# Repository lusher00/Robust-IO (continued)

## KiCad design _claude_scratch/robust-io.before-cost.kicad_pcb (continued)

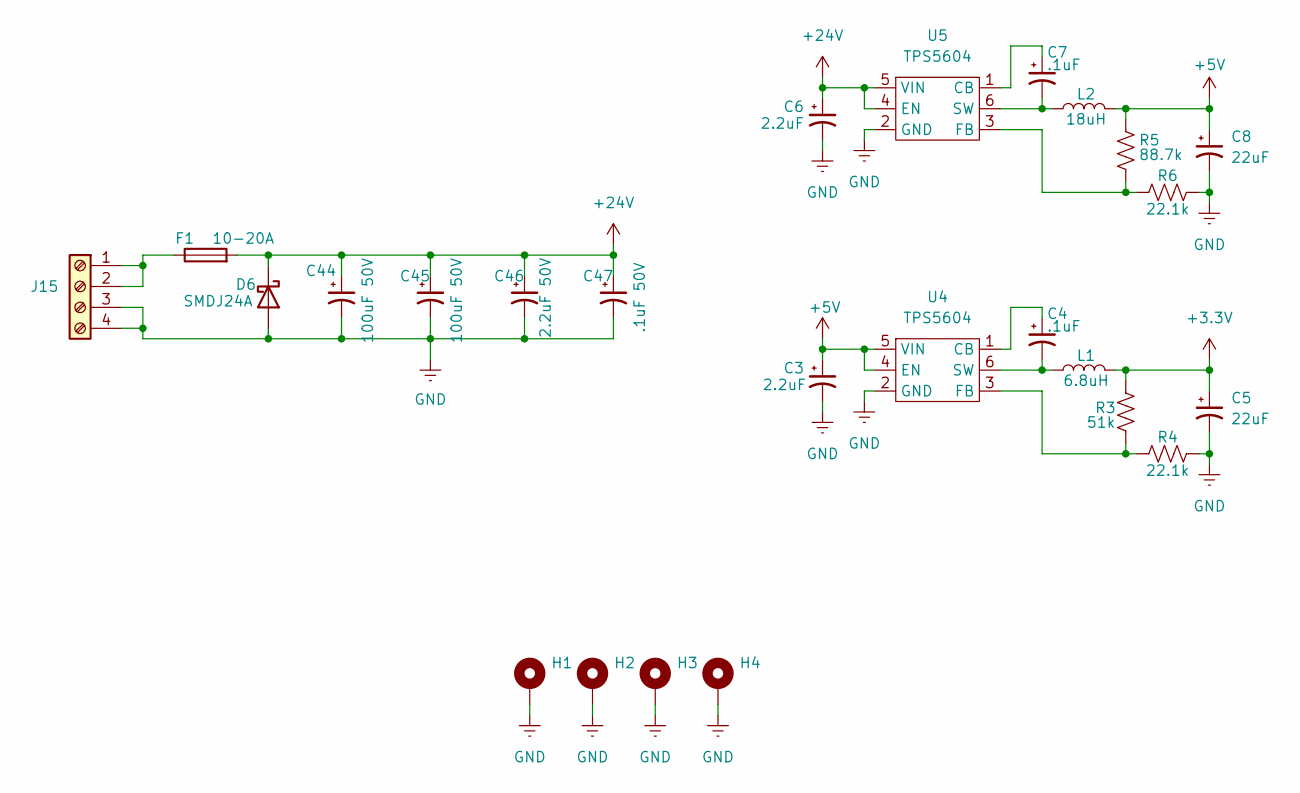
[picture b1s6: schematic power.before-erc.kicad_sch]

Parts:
C3, C6: 2.2uF; C_0805_2012Metric_Pad1.18x1.45mm_HandSolder
C4, C7: .1uF; C_0603_1608Metric_Pad1.08x0.95mm_HandSolder
C5, C8: 22uF; C_0603_1608Metric_Pad1.08x0.95mm_HandSolder
C44, C45: 100uF 50V; CP_Elec_8x10
C46: 2.2uF 50V; C_0805_2012Metric_Pad1.18x1.45mm_HandSolder
C47: .1uF 50V; C_0805_2012Metric_Pad1.18x1.45mm_HandSolder
D6: SMDJ24A; D_SMC
F1: 10-20A; Fuseholder_Blade_Mini_Keystone_3568
H1, H2, H3, H4: MountingHole_Pad; MountingHole_3.2mm_M3_DIN965_Pad_TopBottom
J15: Screw_Terminal_01x04; PhoenixContact_MSTBA_2,5_4-G-5,08_1x04_P5.08mm_Horizontal
L1: 6.8uH; L_0805_2012Metric_Pad1.05x1.20mm_HandSolder; Part Number CB2016T6R8M
L2: 18uH; L_0805_2012Metric
R3: 51k; R_0603_1608Metric_Pad0.98x0.95mm_HandSolder
R4, R6: 22.1k; R_0603_1608Metric_Pad0.98x0.95mm_HandSolder
R5: 88.7k; R_0603_1608Metric_Pad0.98x0.95mm_HandSolder
U4, U5: TPS5604; SOT-23-6

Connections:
+3.3V: C5.1, L1.2, R3.1; also elsewhere on the board
+5V: C3.1, C8.1, L2.2, R5.1, U4.4 (EN), U4.5 (VIN); also elsewhere on the board
+24V: C6.1, C44.1, C45.1, C46.1, C47.1, D6.1 (K), F1.2, U5.4 (EN), U5.5 (VIN); also elsewhere on the board
GND: C3.2, C5.2, C6.2, C8.2, C44.2, C45.2, C46.2, C47.2, D6.2 (A), H1.1 (1_1), H2.1 (1_1), H3.1 (1_1), H4.1 (1_1), J15.3, J15.4, R4.1, R6.1, U4.2 (GND), U5.2 (GND); also elsewhere on the board
unnamed: F1.1, J15.1, J15.2
unnamed: C4.1, U4.1 (CB)
unnamed: R3.2, R4.2, U4.3 (FB)
unnamed: C4.2, L1.1, U4.6 (SW)
unnamed: C7.1, U5.1 (CB)
unnamed: R5.2, R6.2, U5.3 (FB)
unnamed: C7.2, L2.1, U5.6 (SW)

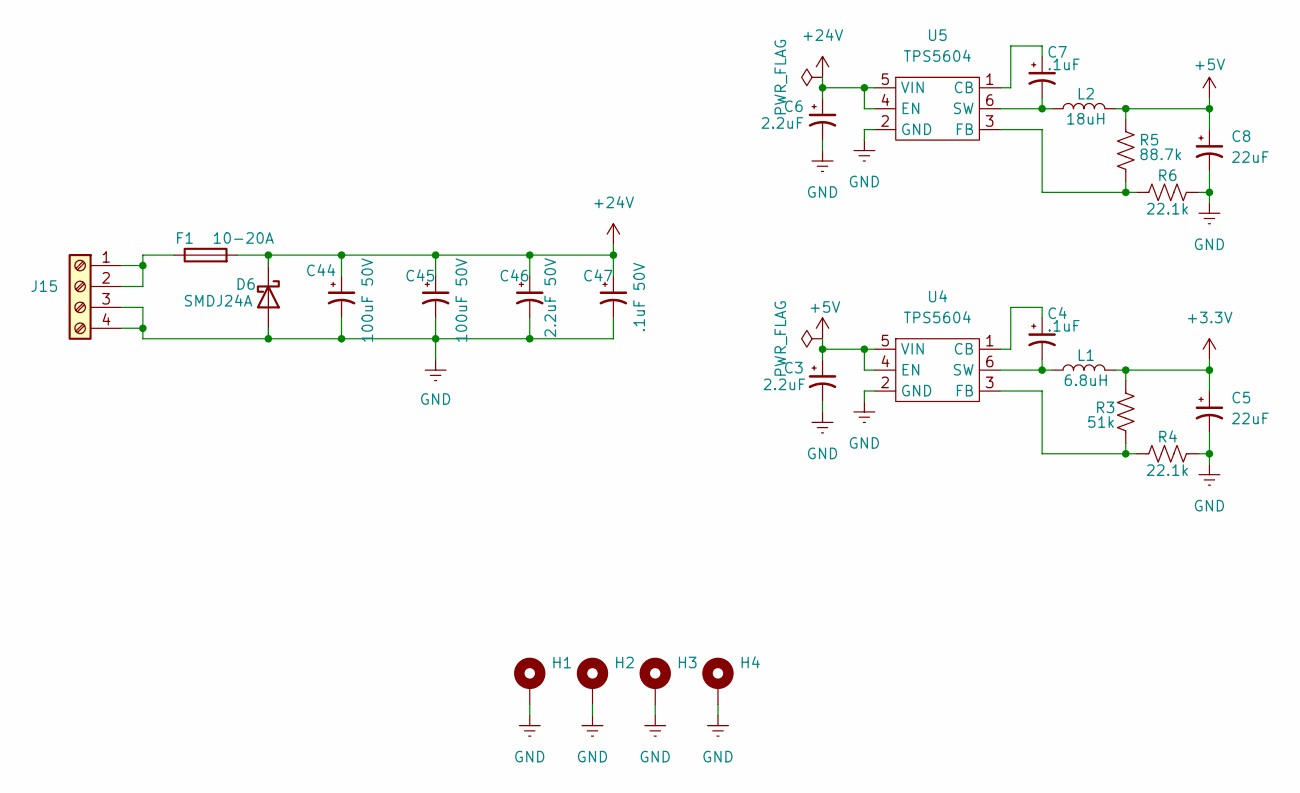
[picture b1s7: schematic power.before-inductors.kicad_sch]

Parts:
C3, C6: 2.2uF; C_0805_2012Metric_Pad1.18x1.45mm_HandSolder
C4, C7: .1uF; C_0603_1608Metric_Pad1.08x0.95mm_HandSolder
C5, C8: 22uF; C_0603_1608Metric_Pad1.08x0.95mm_HandSolder
C44, C45: 100uF 50V; CP_Elec_8x10
C46: 2.2uF 50V; C_0805_2012Metric_Pad1.18x1.45mm_HandSolder
C47: .1uF 50V; C_0805_2012Metric_Pad1.18x1.45mm_HandSolder
D6: SMDJ24A; D_SMC
F1: 10-20A; Fuseholder_Blade_Mini_Keystone_3568
H1, H2, H3, H4: MountingHole_Pad; MountingHole_3.2mm_M3_DIN965_Pad_TopBottom
J15: Screw_Terminal_01x04; PhoenixContact_MSTBA_2,5_4-G-5,08_1x04_P5.08mm_Horizontal
L1: 6.8uH; L_0805_2012Metric_Pad1.05x1.20mm_HandSolder; Part Number CB2016T6R8M
L2: 18uH; L_0805_2012Metric
R3: 51k; R_0603_1608Metric_Pad0.98x0.95mm_HandSolder
R4, R6: 22.1k; R_0603_1608Metric_Pad0.98x0.95mm_HandSolder
R5: 88.7k; R_0603_1608Metric_Pad0.98x0.95mm_HandSolder
U4, U5: TPS5604; SOT-23-6

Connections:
+3.3V: C5.1, L1.2, R3.1; also elsewhere on the board
+5V: C3.1, C8.1, L2.2, R5.1, U4.4 (EN), U4.5 (VIN); also elsewhere on the board
+24V: C6.1, C44.1, C45.1, C46.1, C47.1, D6.1 (K), F1.2, U5.4 (EN), U5.5 (VIN); also elsewhere on the board
GND: C3.2, C5.2, C6.2, C8.2, C44.2, C45.2, C46.2, C47.2, D6.2 (A), H1.1 (1_1), H2.1 (1_1), H3.1 (1_1), H4.1 (1_1), J15.3, J15.4, R4.1, R6.1, U4.2 (GND), U5.2 (GND); also elsewhere on the board
unnamed: F1.1, J15.1, J15.2
unnamed: C4.1, U4.1 (CB)
unnamed: R3.2, R4.2, U4.3 (FB)
unnamed: C4.2, L1.1, U4.6 (SW)
unnamed: C7.1, U5.1 (CB)
unnamed: R5.2, R6.2, U5.3 (FB)
unnamed: C7.2, L2.1, U5.6 (SW)

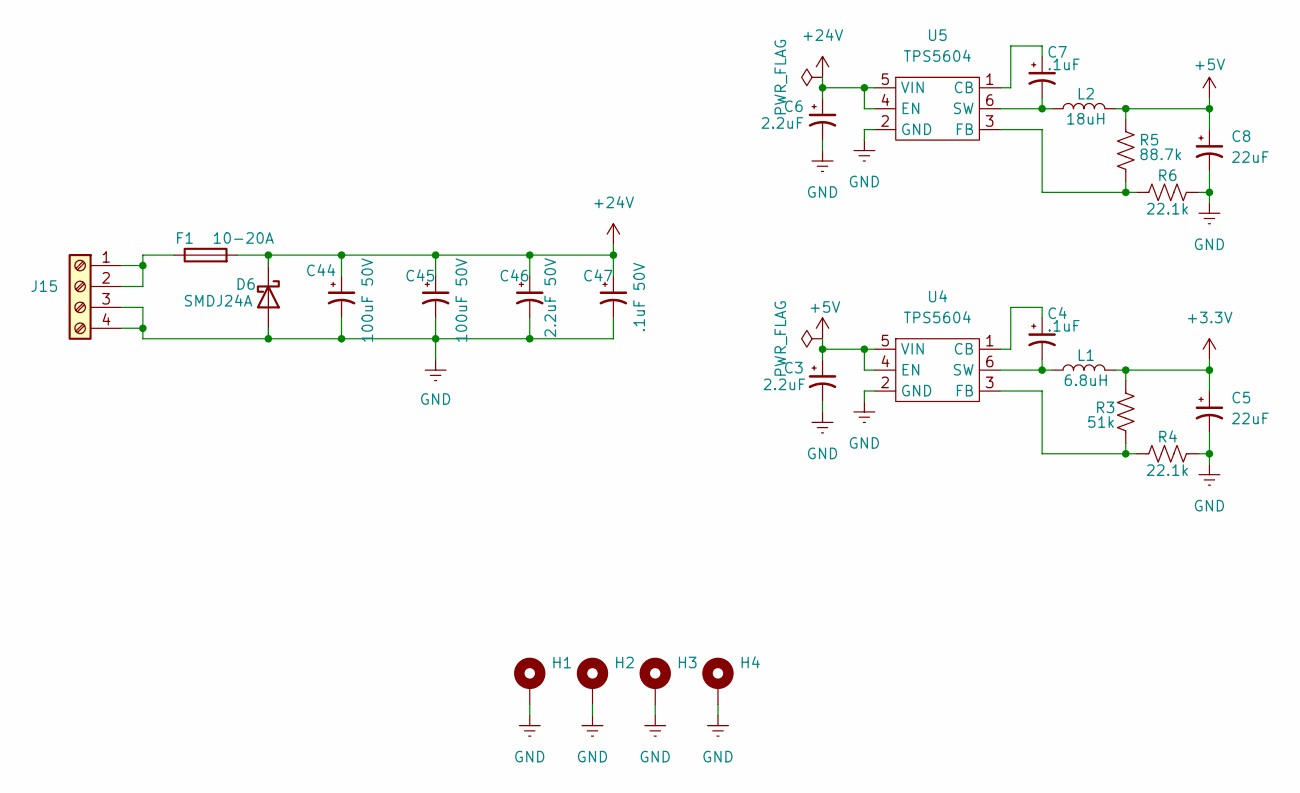
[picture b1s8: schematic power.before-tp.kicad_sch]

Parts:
C3, C6: 2.2uF; C_0805_2012Metric_Pad1.18x1.45mm_HandSolder
C4, C7: .1uF; C_0603_1608Metric_Pad1.08x0.95mm_HandSolder
C5, C8: 22uF; C_0603_1608Metric_Pad1.08x0.95mm_HandSolder
C44, C45: 100uF 50V; CP_Elec_8x10
C46: 2.2uF 50V; C_0805_2012Metric_Pad1.18x1.45mm_HandSolder
C47: .1uF 50V; C_0805_2012Metric_Pad1.18x1.45mm_HandSolder
D6: SMDJ24A; D_SMC
F1: 10-20A; Fuseholder_Blade_Mini_Keystone_3568
H1, H2, H3, H4: MountingHole_Pad; MountingHole_3.2mm_M3_DIN965_Pad_TopBottom
J15: Screw_Terminal_01x04; PhoenixContact_MSTBA_2,5_4-G-5,08_1x04_P5.08mm_Horizontal
L1: 6.8uH; L_Sunlord_SWPA4030S; Part Number CB2016T6R8M
L2: 18uH; L_Sunlord_SWPA4030S
R3: 51k; R_0603_1608Metric_Pad0.98x0.95mm_HandSolder
R4, R6: 22.1k; R_0603_1608Metric_Pad0.98x0.95mm_HandSolder
R5: 88.7k; R_0603_1608Metric_Pad0.98x0.95mm_HandSolder
U4, U5: TPS5604; SOT-23-6

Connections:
+3.3V: C5.1, L1.2, R3.1; also elsewhere on the board
+5V: C3.1, C8.1, L2.2, R5.1, U4.4 (EN), U4.5 (VIN); also elsewhere on the board
+24V: C6.1, C44.1, C45.1, C46.1, C47.1, D6.1 (K), F1.2, U5.4 (EN), U5.5 (VIN); also elsewhere on the board
GND: C3.2, C5.2, C6.2, C8.2, C44.2, C45.2, C46.2, C47.2, D6.2 (A), H1.1 (1_1), H2.1 (1_1), H3.1 (1_1), H4.1 (1_1), J15.3, J15.4, R4.1, R6.1, U4.2 (GND), U5.2 (GND); also elsewhere on the board
unnamed: F1.1, J15.1, J15.2
unnamed: C4.1, U4.1 (CB)
unnamed: R3.2, R4.2, U4.3 (FB)
unnamed: C4.2, L1.1, U4.6 (SW)
unnamed: C7.1, U5.1 (CB)
unnamed: R5.2, R6.2, U5.3 (FB)
unnamed: C7.2, L2.1, U5.6 (SW)

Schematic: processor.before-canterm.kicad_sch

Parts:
C1, C2, C11, C12: 22pF; C_0603_1608Metric
C9, C10, C13, C14, C15, C71, C72, C73: .1uF; C_0603_1608Metric
C16: 1nF; C_0603_1608Metric
C69, C70: 10nF; C_0603_1608Metric
D1, D3: BAT54C; SOT-23
D44, D46: 1N4148W; D_SOD-123
D45, D47: LED; LED_0603_1608Metric
J1: AVR-ISP-6; PinHeader_2x03_P2.54mm_Vertical_SMD
J4: Screw_Terminal_01x04; PhoenixContact_MSTBA_2,5_4-G-5,08_1x04_P5.08mm_Horizontal
L3: 10uH; C_0603_1608Metric
Q3, Q4: 2N7002; SOT-23
R1, R7: 10k; R_0603_1608Metric_Pad0.98x0.95mm_HandSolder
R2: 120; R_0603_1608Metric_Pad0.98x0.95mm_HandSolder
R8, R93, R97: 330; R_0603_1608Metric_Pad0.98x0.95mm_HandSolder
R27: 4.7k; R_0603_1608Metric_Pad0.98x0.95mm_HandSolder
R92, R95: 100k; R_0603_1608Metric_Pad0.98x0.95mm_HandSolder
SW2: B3U-1000P; SW_SPST_B3U-1000P
U2: ATmega1284P-A; TQFP-44_10x10mm_P0.8mm
U3: MCP2515; QFN-20-1EP_4x4mm_P0.5mm_EP2.5x2.5mm
U6: MCP2562-E-MF; DFN-8-1EP_3x3mm_P0.65mm_EP1.6x2.56mm
Y1: 16MHz; WE-XTAL_CFPX-180
Y2: 12MHz; WE-XTAL_CFPX-180

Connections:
+3.3V: C9.1, C15.1, C72.1, C73.1, D1.3, D3.3, J1.2 (VCC), L3.1, R1.1, R7.1, R93.2, R97.2, U2.5 (VCC), U2.17 (VCC), U2.38 (VCC), U3.18 (VDD), U6.5 (Vio); also elsewhere on the board
+5V: J4.3, U6.3 (VDD); also elsewhere on the board
/processor/CS_CAN: U2.40 (PB0), U3.16 (~CS); also elsewhere on the board
/processor/INT_CAN0: U2.11 (PD2), U3.11 (~INT); also elsewhere on the board
/processor/RST: C13.1, J1.5 (~RST), R7.2, SW2.1 (A), U2.4 (~RESET); also elsewhere on the board
/processor/RX0: C69.1, U2.9 (PD0); also elsewhere on the board
/processor/TX0: C70.1, U2.10 (PD1); also elsewhere on the board
AMUX0: D1.1, U2.37 (PA0); also elsewhere on the board
CS_IN0: U2.41 (PB1); also elsewhere on the board
DEN0: U2.43 (PB3); also elsewhere on the board
DEN1: U2.44 (PB4); also elsewhere on the board
DEN2: U2.33 (PA4); also elsewhere on the board
DEN3: U2.32 (PA5); also elsewhere on the board
DRV_OUT0: U2.19 (PC0); also elsewhere on the board
DRV_OUT1: U2.20 (PC1); also elsewhere on the board
DRV_OUT2: U2.21 (PC2); also elsewhere on the board
DRV_OUT3: U2.22 (PC3); also elsewhere on the board
DRV_OUT4: U2.23 (PC4); also elsewhere on the board
DRV_OUT5: U2.24 (PC5); also elsewhere on the board
DRV_OUT6: U2.25 (PC6); also elsewhere on the board
DRV_OUT7: U2.26 (PC7); also elsewhere on the board
DSELn: U2.31 (PA6); also elsewhere on the board
EN_M0: U2.14 (PD5); also elsewhere on the board
EN_M1: U2.16 (PD7); also elsewhere on the board
FAULTMn: U2.12 (PD3); also elsewhere on the board
GND: C1.2, C2.2, C9.2, C10.2, C11.2, C12.2, C13.2, C14.2, C15.2, C16.2, C71.2, C72.2, C73.2, D44.2 (A), D46.2 (A), J1.6 (GND), J4.4, Q3.2 (S), Q4.2 (S), R8.1, R92.1, R95.1, U2.6 (GND), U2.18 (GND), U2.28 (GND), U2.39 (GND), U3.8 (VSS), U6.2 (VSS), U6.8 (SHDN), U6.9 (PAD), Y1.2, Y1.4, Y2.2, Y2.4; also elsewhere on the board
INT_B0: U2.42 (PB2); also elsewhere on the board
IPROPIM0: D3.2, U2.35 (PA2); also elsewhere on the board
IPROPIM1: D3.1, U2.34 (PA3); also elsewhere on the board
ISENSE_PROT: R27.2; also elsewhere on the board
MISO0: J1.1 (MISO), U2.2 (PB6), U3.15 (SO); also elsewhere on the board
MOSI0: J1.4 (MOSI), U2.1 (PB5), U3.14 (SI); also elsewhere on the board
unnamed: C69.2, D44.1 (K), Q3.1 (G), R92.2
unnamed: D45.2 (A), R93.1
unnamed: D45.1 (K), Q3.3 (D)
unnamed: C70.2, D46.1 (K), Q4.1 (G), R95.2
unnamed: D47.2 (A), R97.1
unnamed: D47.1 (K), Q4.3 (D)
unnamed: J4.2, R2.2, U6.6 (CANL)
unnamed: R8.2, SW2.2 (B)
unnamed: C14.1, U2.29 (AREF)
unnamed: C10.1, C71.1, L3.2, U2.27 (AVCC)
unnamed: C16.1, D1.2, R27.1, U2.36 (PA1)
unnamed: C12.1, U2.8 (XTAL1), Y2.1
unnamed: C11.1, U2.7 (XTAL2), Y2.3
unnamed: C2.1, U3.7 (OSC1), Y1.3
unnamed: C1.1, U3.6 (OSC2), Y1.1
unnamed: U3.20 (RXCAN), U6.4 (RXD)
unnamed: U3.19 (TXCAN), U6.1 (TXD)
unnamed: R1.2, U3.17 (~RESET)
PH_M0: U2.13 (PD4); also elsewhere on the board
PH_M1: U2.15 (PD6); also elsewhere on the board
SCLK0: J1.3 (SCK), U2.3 (PB7), U3.12 (SCK); also elsewhere on the board
nSLEEPMn: U2.30 (PA7); also elsewhere on the board

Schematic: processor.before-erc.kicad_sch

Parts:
C1, C2, C11, C12: 22pF; C_0603_1608Metric
C9, C10, C13, C14, C15, C71, C72, C73: .1uF; C_0603_1608Metric
C16: 1nF; C_0603_1608Metric
C69, C70: 10nF; C_0603_1608Metric
D1, D3: BAT54C; SOT-23
D44, D46: 1N4148W; D_SOD-123
D45, D47: LED; LED_0603_1608Metric
D48: SP0502BAHT; SOT-23
J1: AVR-ISP-6; PinHeader_2x03_P2.54mm_Vertical_SMD
J4: Screw_Terminal_01x04; PhoenixContact_MSTBA_2,5_4-G-5,08_1x04_P5.08mm_Horizontal
J20: UART 3V3 (FTDI pinout); PinHeader_1x06_P2.54mm_Vertical
L3: 10uH; C_0603_1608Metric
Q3, Q4: 2N7002; SOT-23
R1, R7: 10k; R_0603_1608Metric_Pad0.98x0.95mm_HandSolder
R2: 120; R_0603_1608Metric_Pad0.98x0.95mm_HandSolder
R8, R93, R97: 330; R_0603_1608Metric_Pad0.98x0.95mm_HandSolder
R27: 4.7k; R_0603_1608Metric_Pad0.98x0.95mm_HandSolder
R92, R95: 100k; R_0603_1608Metric_Pad0.98x0.95mm_HandSolder
R98, R99: 1k; R_0603_1608Metric
SW1: CHS-01TB; SW_DIP_SPSTx01_Slide_Copal_CHS-01B_W7.62mm_P1.27mm
SW2: B3U-1000P; SW_SPST_B3U-1000P
U2: ATmega1284P-A; TQFP-44_10x10mm_P0.8mm
U3: MCP2515; QFN-20-1EP_4x4mm_P0.5mm_EP2.5x2.5mm
U6: MCP2562-E-MF; DFN-8-1EP_3x3mm_P0.65mm_EP1.6x2.56mm
Y1: 16MHz; WE-XTAL_CFPX-180
Y2: 12MHz; WE-XTAL_CFPX-180

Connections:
+3.3V: C9.1, C15.1, C72.1, C73.1, D1.3, D3.3, J1.2 (VCC), L3.1, R1.1, R7.1, R93.2, R97.2, U2.5 (VCC), U2.17 (VCC), U2.38 (VCC), U3.18 (VDD), U6.5 (Vio); also elsewhere on the board
+5V: J4.3, U6.3 (VDD); also elsewhere on the board
/processor/CS_CAN: U2.40 (PB0), U3.16 (~CS); also elsewhere on the board
/processor/INT_CAN0: U2.11 (PD2), U3.11 (~INT); also elsewhere on the board
/processor/RST: C13.1, J1.5 (~RST), R7.2, SW2.1 (A), U2.4 (~RESET); also elsewhere on the board
/processor/RX0: C69.1, R98.1, U2.9 (PD0); also elsewhere on the board
/processor/RX0_EXT: D48.1 (K), J20.4, R98.2
/processor/TX0: C70.1, R99.1, U2.10 (PD1); also elsewhere on the board
/processor/TX0_EXT: D48.2 (K), J20.5, R99.2
AMUX0: D1.1, U2.37 (PA0); also elsewhere on the board
CS_IN0: U2.41 (PB1); also elsewhere on the board
DEN0: U2.43 (PB3); also elsewhere on the board
DEN1: U2.44 (PB4); also elsewhere on the board
DEN2: U2.33 (PA4); also elsewhere on the board
DEN3: U2.32 (PA5); also elsewhere on the board
DRV_OUT0: U2.19 (PC0); also elsewhere on the board
DRV_OUT1: U2.20 (PC1); also elsewhere on the board
DRV_OUT2: U2.21 (PC2); also elsewhere on the board
DRV_OUT3: U2.22 (PC3); also elsewhere on the board
DRV_OUT4: U2.23 (PC4); also elsewhere on the board
DRV_OUT5: U2.24 (PC5); also elsewhere on the board
DRV_OUT6: U2.25 (PC6); also elsewhere on the board
DRV_OUT7: U2.26 (PC7); also elsewhere on the board
DSELn: U2.31 (PA6); also elsewhere on the board
EN_M0: U2.14 (PD5); also elsewhere on the board
EN_M1: U2.16 (PD7); also elsewhere on the board
FAULTMn: U2.12 (PD3); also elsewhere on the board
GND: C1.2, C2.2, C9.2, C10.2, C11.2, C12.2, C13.2, C14.2, C15.2, C16.2, C71.2, C72.2, C73.2, D44.2 (A), D46.2 (A), D48.3 (A), J1.6 (GND), J4.4, J20.1, J20.2, Q3.2 (S), Q4.2 (S), R8.1, R92.1, R95.1, U2.6 (GND), U2.18 (GND), U2.28 (GND), U2.39 (GND), U3.8 (VSS), U6.2 (VSS), U6.8 (SHDN), U6.9 (PAD), Y1.2, Y1.4, Y2.2, Y2.4; also elsewhere on the board
INT_B0: U2.42 (PB2); also elsewhere on the board
IPROPIM0: D3.2, U2.35 (PA2); also elsewhere on the board
IPROPIM1: D3.1, U2.34 (PA3); also elsewhere on the board
ISENSE_PROT: R27.2; also elsewhere on the board
MISO0: J1.1 (MISO), U2.2 (PB6), U3.15 (SO); also elsewhere on the board
MOSI0: J1.4 (MOSI), U2.1 (PB5), U3.14 (SI); also elsewhere on the board
unnamed: C69.2, D44.1 (K), Q3.1 (G), R92.2
unnamed: D45.2 (A), R93.1
unnamed: D45.1 (K), Q3.3 (D)
unnamed: C70.2, D46.1 (K), Q4.1 (G), R95.2
unnamed: D47.2 (A), R97.1
unnamed: D47.1 (K), Q4.3 (D)
unnamed: J4.2, R2.2, U6.6 (CANL)
unnamed: R8.2, SW2.2 (B)
unnamed: C14.1, U2.29 (AREF)
unnamed: C10.1, C71.1, L3.2, U2.27 (AVCC)
unnamed: C16.1, D1.2, R27.1, U2.36 (PA1)
unnamed: C12.1, U2.8 (XTAL1), Y2.1
unnamed: C11.1, U2.7 (XTAL2), Y2.3
unnamed: C2.1, U3.7 (OSC1), Y1.3
unnamed: C1.1, U3.6 (OSC2), Y1.1
unnamed: U3.20 (RXCAN), U6.4 (RXD)
unnamed: U3.19 (TXCAN), U6.1 (TXD)
unnamed: R1.2, U3.17 (~RESET)
PH_M0: U2.13 (PD4); also elsewhere on the board
PH_M1: U2.15 (PD6); also elsewhere on the board
SCLK0: J1.3 (SCK), U2.3 (PB7), U3.12 (SCK); also elsewhere on the board
nSLEEPMn: U2.30 (PA7); also elsewhere on the board

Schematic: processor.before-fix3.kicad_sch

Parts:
C1, C2, C11, C12: 22pF; C_0603_1608Metric
C9, C10, C13, C14, C15, C71, C72, C73: .1uF; C_0603_1608Metric
C16: 1nF; C_0603_1608Metric
C69, C70: 10nF; C_0603_1608Metric
D1, D3: BAT54C; SOT-23
D44, D46: 1N4148W; D_SOD-123
D45, D47: LED; LED_0603_1608Metric
D48: SP0502BAHT; SOT-23
J1: AVR-ISP-6; PinHeader_2x03_P2.54mm_Vertical_SMD
J4: Screw_Terminal_01x04; PhoenixContact_MSTBA_2,5_4-G-5,08_1x04_P5.08mm_Horizontal
J20: UART 3V3 (FTDI pinout); PinHeader_1x06_P2.54mm_Vertical
L3: 10uH; C_0603_1608Metric
Q3, Q4: 2N7002; SOT-23
R1, R7: 10k; R_0603_1608Metric_Pad0.98x0.95mm_HandSolder
R2: 120; R_0603_1608Metric_Pad0.98x0.95mm_HandSolder
R8, R93, R97: 330; R_0603_1608Metric_Pad0.98x0.95mm_HandSolder
R27: 4.7k; R_0603_1608Metric_Pad0.98x0.95mm_HandSolder
R92, R95: 100k; R_0603_1608Metric_Pad0.98x0.95mm_HandSolder
R98, R99: 1k; R_0603_1608Metric
SW1: CHS-01TB; SW_DIP_SPSTx01_Slide_Copal_CHS-01B_W7.62mm_P1.27mm
SW2: B3U-1000P; SW_SPST_B3U-1000P
TP8: CS_CAN; TestPoint_Pad_D1.0mm
TP10: INT_CAN0; TestPoint_Pad_D1.0mm
TP11: RST; TestPoint_Pad_D1.0mm
TP12: RX0; TestPoint_Pad_D1.0mm
TP13: TX0; TestPoint_Pad_D1.0mm
U2: ATmega1284P-A; TQFP-44_10x10mm_P0.8mm
U3: MCP2515; QFN-20-1EP_4x4mm_P0.5mm_EP2.5x2.5mm
U6: MCP2562-E-MF; DFN-8-1EP_3x3mm_P0.65mm_EP1.6x2.56mm
Y1: 16MHz; WE-XTAL_CFPX-180
Y2: 12MHz; WE-XTAL_CFPX-180

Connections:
+3.3V: C9.1, C15.1, C72.1, C73.1, D1.3, D3.3, J1.2 (VCC), L3.1, R1.1, R7.1, R93.2, R97.2, U2.5 (VCC), U2.17 (VCC), U2.38 (VCC), U3.18 (VDD), U6.5 (Vio); also elsewhere on the board
+5V: J4.3, U6.3 (VDD); also elsewhere on the board
/processor/CS_CAN: TP8.1, U2.40 (PB0), U3.16 (~CS)
/processor/INT_CAN0: TP10.1, U2.11 (PD2), U3.11 (~INT)
/processor/RST: C13.1, J1.5 (~RST), R7.2, SW2.1 (A), TP11.1, U2.4 (~RESET)
/processor/RX0: C69.1, R98.1, TP12.1, U2.9 (PD0)
/processor/RX0_EXT: D48.1 (K), J20.4, R98.2
/processor/TX0: C70.1, R99.1, TP13.1, U2.10 (PD1)
/processor/TX0_EXT: D48.2 (K), J20.5, R99.2
AMUX0: D1.1, U2.37 (PA0); also elsewhere on the board
CS_IN0: U2.41 (PB1); also elsewhere on the board
DEN0: U2.43 (PB3); also elsewhere on the board
DEN1: U2.44 (PB4); also elsewhere on the board
DEN2: U2.33 (PA4); also elsewhere on the board
DEN3: U2.32 (PA5); also elsewhere on the board
DRV_OUT0: U2.19 (PC0); also elsewhere on the board
DRV_OUT1: U2.20 (PC1); also elsewhere on the board
DRV_OUT2: U2.21 (PC2); also elsewhere on the board
DRV_OUT3: U2.22 (PC3); also elsewhere on the board
DRV_OUT4: U2.23 (PC4); also elsewhere on the board
DRV_OUT5: U2.24 (PC5); also elsewhere on the board
DRV_OUT6: U2.25 (PC6); also elsewhere on the board
DRV_OUT7: U2.26 (PC7); also elsewhere on the board
DSELn: U2.31 (PA6); also elsewhere on the board
EN_M0: U2.14 (PD5); also elsewhere on the board
EN_M1: U2.16 (PD7); also elsewhere on the board
FAULTMn: U2.12 (PD3); also elsewhere on the board
GND: C1.2, C2.2, C9.2, C10.2, C11.2, C12.2, C13.2, C14.2, C15.2, C16.2, C71.2, C72.2, C73.2, D44.2 (A), D46.2 (A), D48.3 (A), J1.6 (GND), J4.4, J20.1, J20.2, Q3.2 (S), Q4.2 (S), R8.1, R92.1, R95.1, U2.6 (GND), U2.18 (GND), U2.28 (GND), U2.39 (GND), U3.8 (VSS), U6.2 (VSS), U6.8 (SHDN), U6.9 (PAD), Y1.2, Y1.4, Y2.2, Y2.4; also elsewhere on the board
INT_B0: U2.42 (PB2); also elsewhere on the board
IPROPIM0: D3.2, U2.35 (PA2); also elsewhere on the board
IPROPIM1: D3.1, U2.34 (PA3); also elsewhere on the board
ISENSE_PROT: R27.2; also elsewhere on the board
MISO0: J1.1 (MISO), U2.2 (PB6), U3.15 (SO); also elsewhere on the board
MOSI0: J1.4 (MOSI), U2.1 (PB5), U3.14 (SI); also elsewhere on the board
unnamed: C69.2, D44.1 (K), Q3.1 (G), R92.2
unnamed: D45.2 (A), R93.1
unnamed: D45.1 (K), Q3.3 (D)
unnamed: C70.2, D46.1 (K), Q4.1 (G), R95.2
unnamed: D47.2 (A), R97.1
unnamed: D47.1 (K), Q4.3 (D)
unnamed: J4.2, R2.2, U6.6 (CANL)
unnamed: R8.2, SW2.2 (B)
unnamed: C14.1, U2.29 (AREF)
unnamed: C10.1, C71.1, L3.2, U2.27 (AVCC)
unnamed: C16.1, D1.2, R27.1, U2.36 (PA1)
unnamed: C12.1, U2.8 (XTAL1), Y2.1
unnamed: C11.1, U2.7 (XTAL2), Y2.3
unnamed: C2.1, U3.7 (OSC1), Y1.3
unnamed: C1.1, U3.6 (OSC2), Y1.1
unnamed: U3.20 (RXCAN), U6.4 (RXD)
unnamed: U3.19 (TXCAN), U6.1 (TXD)
unnamed: R1.2, U3.17 (~RESET)
PH_M0: U2.13 (PD4); also elsewhere on the board
PH_M1: U2.15 (PD6); also elsewhere on the board
SCLK0: J1.3 (SCK), U2.3 (PB7), U3.12 (SCK); also elsewhere on the board
nSLEEPMn: U2.30 (PA7); also elsewhere on the board

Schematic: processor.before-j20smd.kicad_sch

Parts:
C1, C2, C11, C12: 22pF; C_0603_1608Metric
C9, C10, C13, C14, C15, C71, C72, C73: .1uF; C_0603_1608Metric
C16: 1nF; C_0603_1608Metric
C69, C70: 10nF; C_0603_1608Metric
D1, D3: BAT54C; SOT-23
D44, D46: 1N4148W; D_SOD-123
D45, D47: LED; LED_0603_1608Metric
D48: SP0502BAHT; SOT-23
J1: AVR-ISP-6; PinHeader_2x03_P2.54mm_Vertical_SMD
J4: Screw_Terminal_01x04; PhoenixContact_MSTBA_2,5_4-G-5,08_1x04_P5.08mm_Horizontal
J20: UART 3V3 (FTDI pinout); PinHeader_1x06_P2.54mm_Vertical
L3: 10uH; C_0603_1608Metric
Q3, Q4: 2N7002; SOT-23
R1, R7: 10k; R_0603_1608Metric_Pad0.98x0.95mm_HandSolder
R2: 120; R_0603_1608Metric_Pad0.98x0.95mm_HandSolder
R8, R93, R97: 330; R_0603_1608Metric_Pad0.98x0.95mm_HandSolder
R27: 4.7k; R_0603_1608Metric_Pad0.98x0.95mm_HandSolder
R92, R95: 100k; R_0603_1608Metric_Pad0.98x0.95mm_HandSolder
R98, R99: 1k; R_0603_1608Metric
SW1: CHS-01TB; SW_DIP_SPSTx01_Slide_Copal_CHS-01B_W7.62mm_P1.27mm
SW2: B3U-1000P; SW_SPST_B3U-1000P
TP8: CS_CAN; TestPoint_Pad_D1.0mm
TP10: INT_CAN0; TestPoint_Pad_D1.0mm
TP11: RST; TestPoint_Pad_D1.0mm
TP12: RX0; TestPoint_Pad_D1.0mm
TP13: TX0; TestPoint_Pad_D1.0mm
U2: ATmega1284P-A; TQFP-44_10x10mm_P0.8mm
U3: MCP2515; QFN-20-1EP_4x4mm_P0.5mm_EP2.5x2.5mm
U6: MCP2562-E-MF; DFN-8-1EP_3x3mm_P0.65mm_EP1.6x2.56mm
Y1: 16MHz; WE-XTAL_CFPX-180
Y2: 12MHz; WE-XTAL_CFPX-180

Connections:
+3.3V: C9.1, C15.1, C72.1, C73.1, D1.3, D3.3, J1.2 (VCC), L3.1, R1.1, R7.1, R93.2, R97.2, U2.5 (VCC), U2.17 (VCC), U2.38 (VCC), U3.18 (VDD), U6.5 (Vio); also elsewhere on the board
+5V: J4.3, U6.3 (VDD); also elsewhere on the board
/processor/CS_CAN: TP8.1, U2.40 (PB0), U3.16 (~CS)
/processor/INT_CAN0: TP10.1, U2.11 (PD2), U3.11 (~INT)
/processor/RST: C13.1, J1.5 (~RST), R7.2, SW2.1 (A), TP11.1, U2.4 (~RESET)
/processor/RX0: C69.1, R98.1, TP12.1, U2.9 (PD0)
/processor/RX0_EXT: D48.1 (K), J20.4, R98.2
/processor/TX0: C70.1, R99.1, TP13.1, U2.10 (PD1)
/processor/TX0_EXT: D48.2 (K), J20.5, R99.2
AMUX0: D1.1, U2.37 (PA0); also elsewhere on the board
CS_IN0: U2.41 (PB1); also elsewhere on the board
DEN0: U2.43 (PB3); also elsewhere on the board
DEN1: U2.44 (PB4); also elsewhere on the board
DEN2: U2.33 (PA4); also elsewhere on the board
DEN3: U2.32 (PA5); also elsewhere on the board
DRV_OUT0: U2.19 (PC0); also elsewhere on the board
DRV_OUT1: U2.20 (PC1); also elsewhere on the board
DRV_OUT2: U2.21 (PC2); also elsewhere on the board
DRV_OUT3: U2.22 (PC3); also elsewhere on the board
DRV_OUT4: U2.23 (PC4); also elsewhere on the board
DRV_OUT5: U2.24 (PC5); also elsewhere on the board
DRV_OUT6: U2.25 (PC6); also elsewhere on the board
DRV_OUT7: U2.26 (PC7); also elsewhere on the board
DSELn: U2.31 (PA6); also elsewhere on the board
EN_M0: U2.14 (PD5); also elsewhere on the board
EN_M1: U2.16 (PD7); also elsewhere on the board
FAULTMn: U2.12 (PD3); also elsewhere on the board
GND: C1.2, C2.2, C9.2, C10.2, C11.2, C12.2, C13.2, C14.2, C15.2, C16.2, C71.2, C72.2, C73.2, D44.2 (A), D46.2 (A), D48.3 (A), J1.6 (GND), J4.4, J20.1, J20.2, Q3.2 (S), Q4.2 (S), R8.1, R92.1, R95.1, U2.6 (GND), U2.18 (GND), U2.28 (GND), U2.39 (GND), U3.8 (VSS), U6.2 (VSS), U6.8 (SHDN), U6.9 (PAD), Y1.2, Y1.4, Y2.2, Y2.4; also elsewhere on the board
INT_B0: U2.42 (PB2); also elsewhere on the board
IPROPIM0: D3.2, U2.35 (PA2); also elsewhere on the board
IPROPIM1: D3.1, U2.34 (PA3); also elsewhere on the board
ISENSE_PROT: R27.2; also elsewhere on the board
MISO0: J1.1 (MISO), U2.2 (PB6), U3.15 (SO); also elsewhere on the board
MOSI0: J1.4 (MOSI), U2.1 (PB5), U3.14 (SI); also elsewhere on the board
unnamed: C69.2, D44.1 (K), Q3.1 (G), R92.2
unnamed: D45.2 (A), R93.1
unnamed: D45.1 (K), Q3.3 (D)
unnamed: C70.2, D46.1 (K), Q4.1 (G), R95.2
unnamed: D47.2 (A), R97.1
unnamed: D47.1 (K), Q4.3 (D)
unnamed: J4.2, R2.2, U6.6 (CANL)
unnamed: R8.2, SW2.2 (B)
unnamed: C14.1, U2.29 (AREF)
unnamed: C10.1, C71.1, L3.2, U2.27 (AVCC)
unnamed: C16.1, D1.2, R27.1, U2.36 (PA1)
unnamed: C12.1, U2.8 (XTAL1), Y2.1
unnamed: C11.1, U2.7 (XTAL2), Y2.3
unnamed: C2.1, U3.7 (OSC1), Y1.3
unnamed: C1.1, U3.6 (OSC2), Y1.1
unnamed: U3.20 (RXCAN), U6.4 (RXD)
unnamed: U3.19 (TXCAN), U6.1 (TXD)
unnamed: R1.2, U3.17 (~RESET)
PH_M0: U2.13 (PD4); also elsewhere on the board
PH_M1: U2.15 (PD6); also elsewhere on the board
SCLK0: J1.3 (SCK), U2.3 (PB7), U3.12 (SCK); also elsewhere on the board
nSLEEPMn: U2.30 (PA7); also elsewhere on the board

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
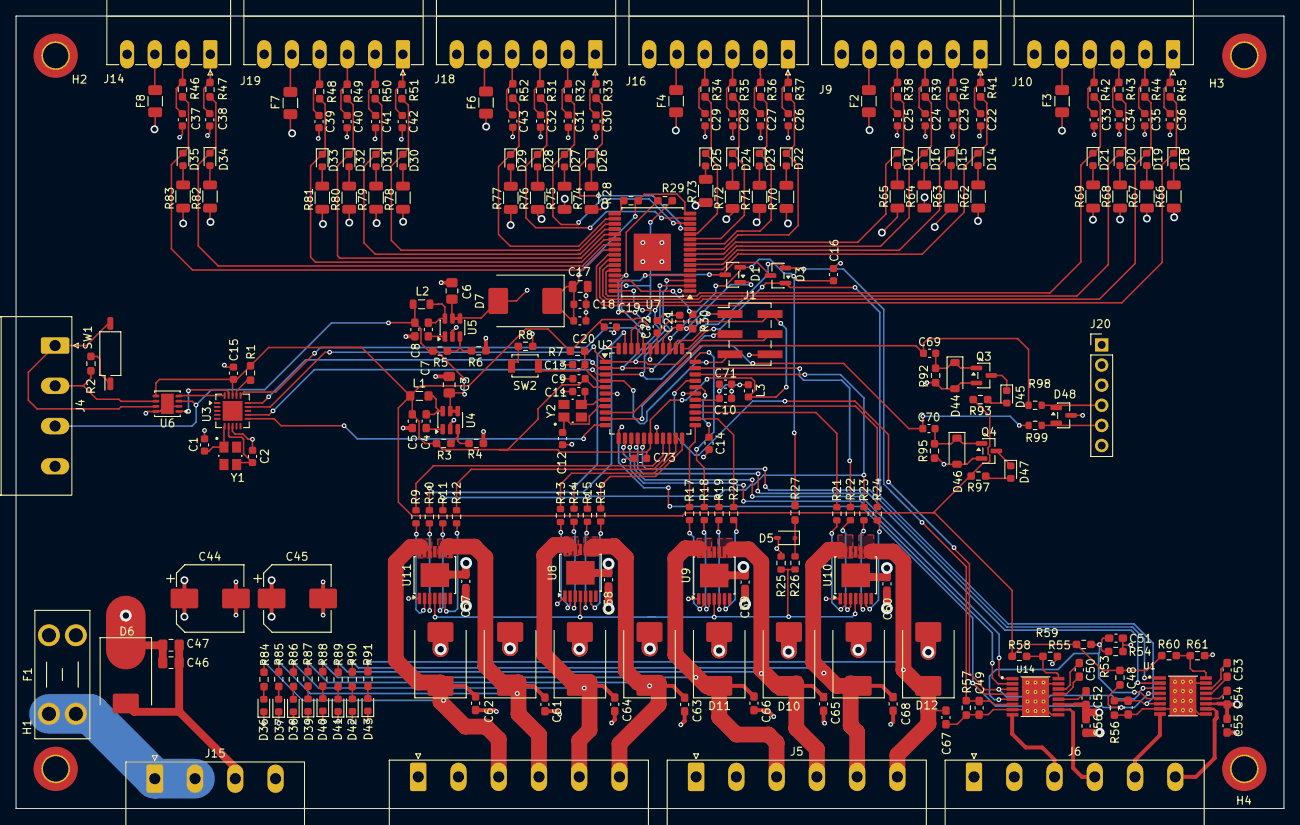
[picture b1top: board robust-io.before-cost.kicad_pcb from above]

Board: 4 copper layers, 160.0 x 100.0 mm, 263 parts (0 on the bottom side), 187 nets.

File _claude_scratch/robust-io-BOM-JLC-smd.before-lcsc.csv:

Comment,Designator,Footprint,LCSC Part #
22pF,"C1,C2,C11,C12",C_0603_1608Metric,C1653
2.2uF 50V,"C3,C6,C46",C_0805_2012Metric,C377773
100nF 50V,"C4,C7,C9,C10,C13,C14,C15,C18,C20,C21,C22,C23,C24,C25,C26,C27,C28,C29,C30,C31,C32,C33,C34,C35,C36,C37,C38,C39,C40,C41,C42,C43,C48,C49,C51,C52,C54,C55,C56,C57,C58,C59,C60,C61,C62,C63,C64,C65,C66,C67,C68,C71,C72,C73",C_0603_1608Metric,C14663
22uF,"C5,C8",C_0603_1608Metric,
1nF,"C16,C19",C_0603_1608Metric,C1588
10uF 50V,C17,C_0805_2012Metric,C440198
100uF 50V,"C44,C45",CP_Elec_8x10,
100nF 50V,C47,C_0805_2012Metric,
22nF,"C50,C53",C_0603_1608Metric,C21122
10nF,"C69,C70",C_0603_1608Metric,C57112
BAT54C,"D1,D3",SOT-23,
B560C,"D2,D4,D8,D9,D10,D11,D12,D13",D_SMC,
BZX384C6V8,D5,D_SOD-323,
SMDJ24A,D6,D_SMC,
B340,D7,D_SMC,
LED,"D14,D15,D16,D17,D18,D19,D20,D21,D22,D23,D24,D25,D26,D27,D28,D29,D30,D31,D32,D33,D34,D35,D36,D37,D38,D39,D40,D41,D42,D43,D45,D47",LED_0603_1608Metric,
1N4148W,"D44,D46",D_SOD-123,
SP0502BAHT,D48,SOT-23,
Polyfuse,"F2,F3,F4,F6,F7,F8",Fuse_1206_3216Metric,
AVR-ISP-6,J1,PinHeader_2x03_P2.54mm_Vertical_SMD,
6.8uH,L1,L_0805_2012Metric,
18uH,L2,L_0805_2012Metric,
10uH,L3,C_0603_1608Metric,
2N7002,"Q3,Q4",SOT-23,
10k,"R1,R7,R28,R29,R53",R_0603_1608Metric,
120,R2,R_0603_1608Metric,
51k,R3,R_0603_1608Metric,
22.1k,"R4,R6",R_0603_1608Metric,
88.7k,R5,R_0603_1608Metric,
330,"R8,R93,R97",R_0603_1608Metric,
4.7k,"R9,R10,R11,R12,R13,R14,R15,R16,R17,R18,R19,R20,R21,R22,R23,R24,R26,R27",R_0603_1608Metric,
750,R25,R_0603_1608Metric,
1k,"R30,R98,R99",R_0603_1608Metric,
100,"R31,R32,R33,R34,R35,R36,R37,R38,R39,R40,R41,R42,R43,R44,R45,R46,R47,R48,R49,R50,R51,R52",R_0603_1608Metric,
16.2k 1%,R54,R_0603_1608Metric,
10k 1%,R55,R_0603_1608Metric,
1.5k 1%,"R56,R57",R_0603_1608Metric,
0,"R59,R61",R_0603_1608Metric,
2.2k,"R62,R63,R64,R65,R66,R67,R68,R69,R70,R71,R72,R73,R74,R75,R76,R77,R78,R79,R80,R81,R82,R83",R_1206_3216Metric,
2.2k,"R84,R85,R86,R87,R88,R89,R90,R91",R_0603_1608Metric,
100k,"R92,R95",R_0603_1608Metric,
CHS-01TB,SW1,SW_DIP_SPSTx01_Slide_Copal_CHS-01B_W7.62mm_P1.27mm,
B3U-1000P,SW2,SW_SPST_B3U-1000P,
DRV8876,"U1,U14",IC_DRV8876PWPR,
ATmega1284P-A,U2,TQFP-44_10x10mm_P0.8mm,
MCP2515,U3,QFN-20-1EP_4x4mm_P0.5mm_EP2.5x2.5mm,
TPS5604,"U4,U5",SOT-23-6,
MCP2562-E-MF,U6,DFN-8-1EP_3x3mm_P0.65mm_EP1.6x2.56mm,
MC33978,U7,HSOP-32-1EP_7.5x11mm_P0.65mm_EP4.7x4.7mm,
BTS7008,"U8,U9,U10,U11",TSSOP-14-1EP_4.4x5mm_P0.65mm,
16MHz,Y1,WE-XTAL_CFPX-180,
12MHz,Y2,WE-XTAL_CFPX-180,
